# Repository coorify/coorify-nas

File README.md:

# coorify-nas

丐版 NAS,本项提供多种不同主板的 AIO 主机外壳模型及状态显示屏幕配套的软硬件资料，希望本项目能给以您一定的帮助！！！

## 支持主板

- 19026P

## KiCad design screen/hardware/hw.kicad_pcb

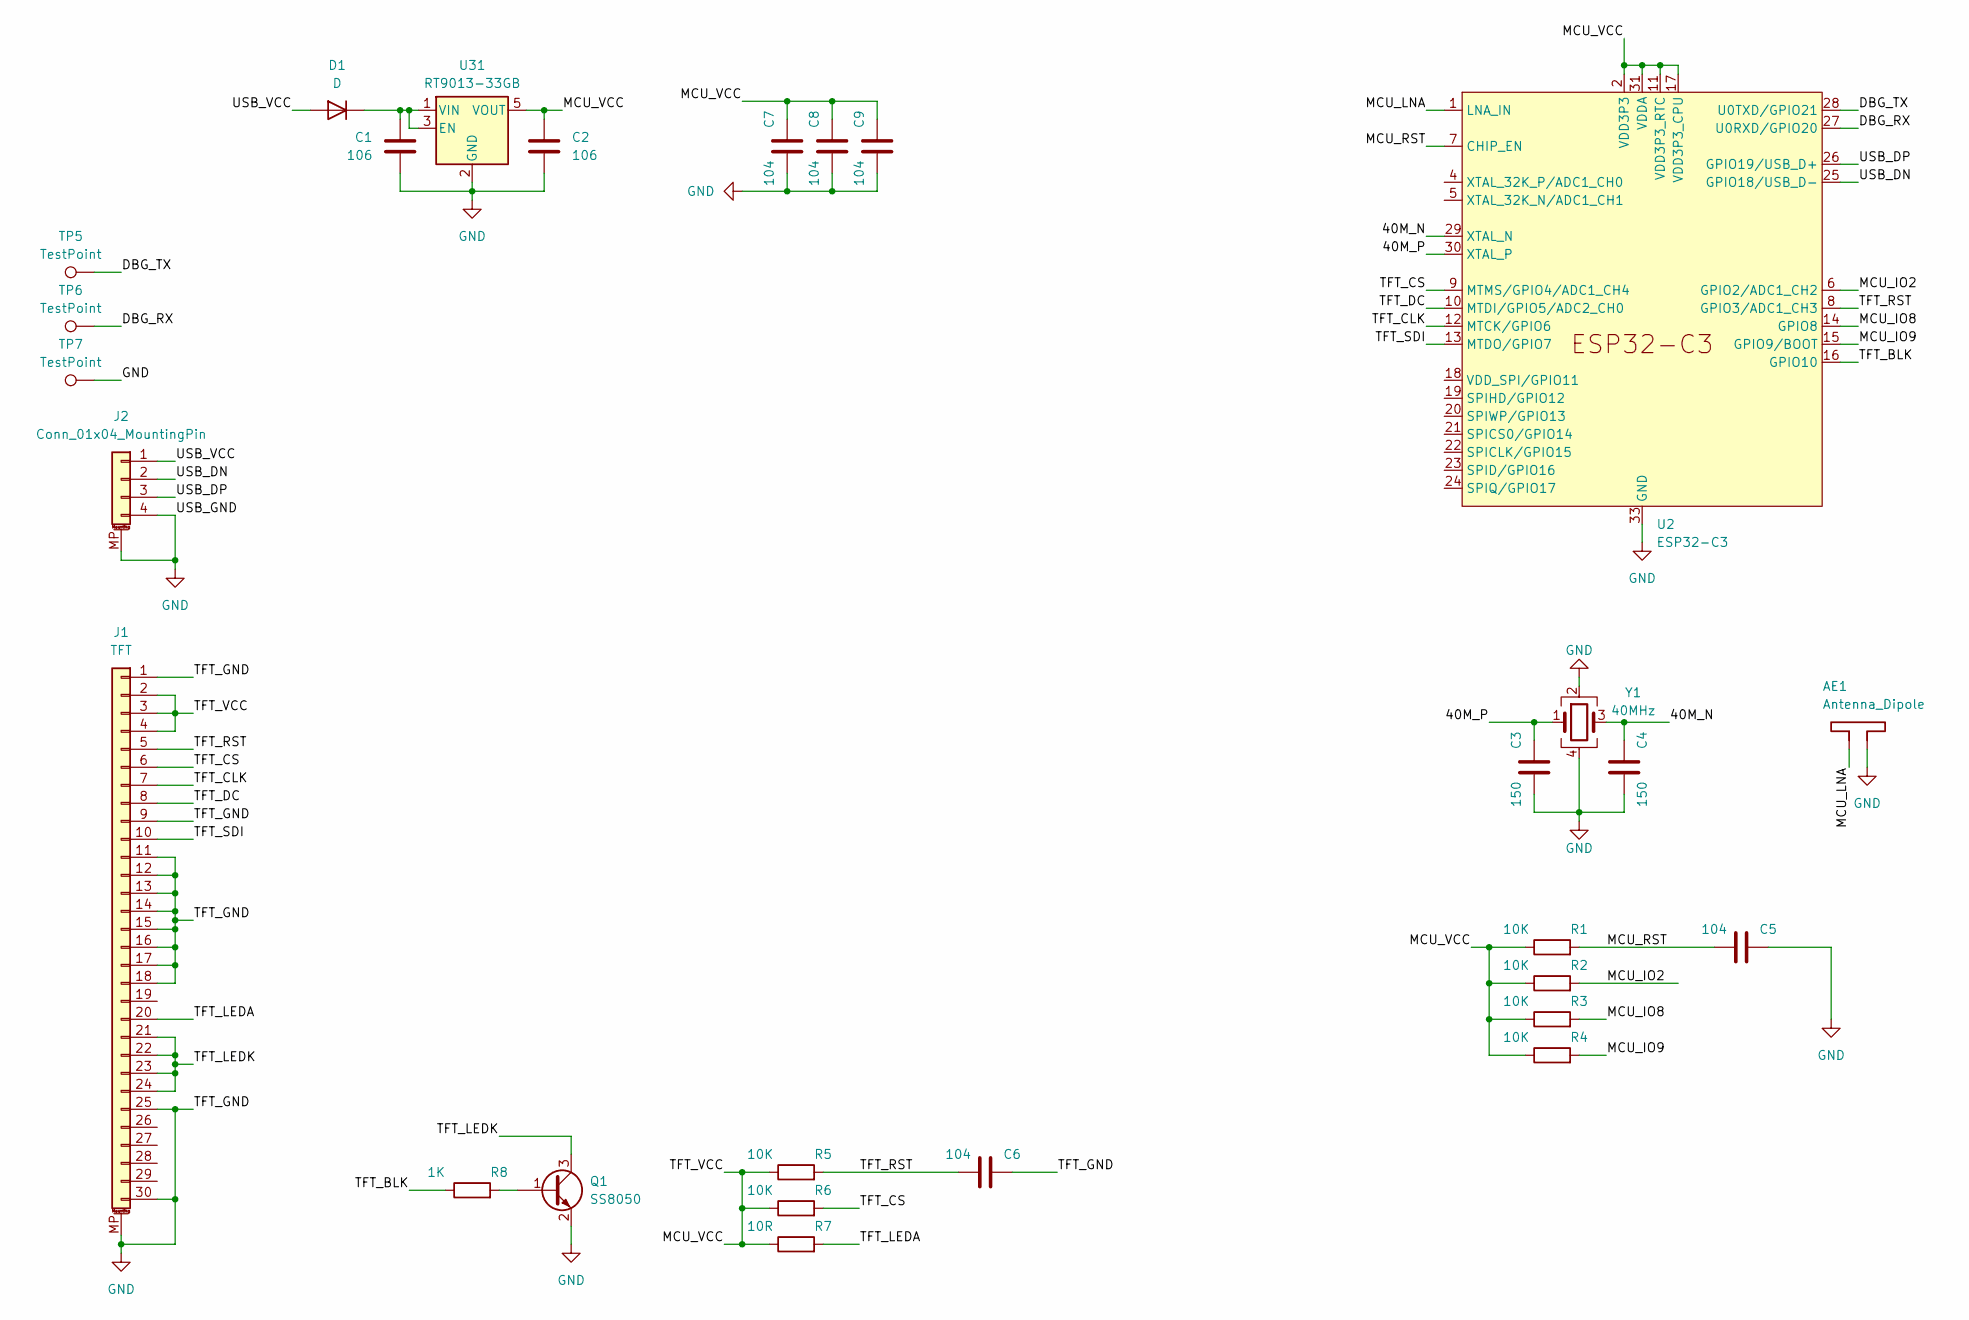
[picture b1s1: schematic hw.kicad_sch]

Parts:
AE1: Antenna_Dipole; Texas_SWRA117D_2.4GHz_Left
C1, C2: 106; C_0603_1608Metric
C3, C4: 150; C_0402_1005Metric
C5, C6, C7, C8, C9: 104; C_0402_1005Metric
D1: D; D_SOD-123
J1: TFT; Hirose_FH12-30S-0.5SH_1x30-1MP_P0.50mm_Horizontal
J2: Conn_01x04_MountingPin; JST_PH_B4B-PH-SM4-TB_1x04-1MP_P2.00mm_Vertical
Q1: SS8050; SOT-23
R1, R2, R3, R4, R5, R6: 10K; R_0402_1005Metric
R7: 10R; R_0402_1005Metric
R8: 1K; R_0402_1005Metric
TP5, TP6, TP7: TestPoint; TestPoint_Pad_D1.0mm
U2: ESP32-C3; QFN-32-1EP_5x5mm_P0.5mm_EP3.45x3.45mm
U31: RT9013-33GB; SOT-23-5
Y1: 40MHz; Crystal_SMD_2016-4Pin_2.0x1.6mm

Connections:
/40M_N: C4.2, U2.29 (XTAL_N), Y1.3
/40M_P: C3.2, U2.30 (XTAL_P), Y1.1
/DBG_RX: TP6.1, U2.27 (U0RXD/GPIO20)
/DBG_TX: TP5.1, U2.28 (U0TXD/GPIO21)
/MCU_IO2: R2.2, U2.6 (GPIO2/ADC1_CH2)
/MCU_IO8: R3.2, U2.14 (GPIO8)
/MCU_IO9: R4.2, U2.15 (GPIO9/BOOT)
/MCU_LNA: AE1.1, U2.1 (LNA_IN)
/MCU_RST: C5.1, R1.2, U2.7 (CHIP_EN)
/MCU_VCC: C2.1, C7.2, C8.2, C9.2, J1.2, J1.3, J1.4, R1.1, R2.1, R3.1, R4.1, R5.1, R6.1, R7.1, U2.2 (VDD3P3), U2.3 (VDD3P3), U2.11 (VDD3P3_RTC), U2.17 (VDD3P3_CPU), U2.31 (VDDA), U2.32 (VDDA); also elsewhere on the board
/TFT_BLK: R8.1, U2.16 (GPIO10)
/TFT_CLK: J1.7, U2.12 (MTCK/GPIO6)
/TFT_CS: J1.6, R6.2, U2.9 (MTMS/GPIO4/ADC1_CH4)
/TFT_DC: J1.8, U2.10 (MTDI/GPIO5/ADC2_CH0)
/TFT_LEDA: J1.20, R7.2
/TFT_LEDK: J1.21, J1.22, J1.23, J1.24, Q1.3 (C)
/TFT_RST: C6.1, J1.5, R5.2, U2.8 (GPIO3/ADC1_CH3)
/TFT_SDI: J1.10, U2.13 (MTDO/GPIO7)
/USB_DN: J2.2, U2.25 (GPIO18/USB_D-)
/USB_DP: J2.3, U2.26 (GPIO19/USB_D+)
/USB_VCC: D1.2 (A), J2.1
GND: AE1.2, C1.2, C2.2, C3.1, C4.1, C5.2, C6.2, C7.1, C8.1, C9.1, J1.1, J1.9, J1.11, J1.12, J1.13, J1.14, J1.15, J1.16, J1.17, J1.18, J1.25, J1.30, J1.MP (MountPin), J2.4, J2.MP (MountPin), Q1.2 (E), TP7.1, U2.33 (GND), Y1.2, Y1.4; also elsewhere on the board
unnamed 22: C1.1, D1.1 (K); also elsewhere on the board
unnamed: Q1.1 (B), R8.2

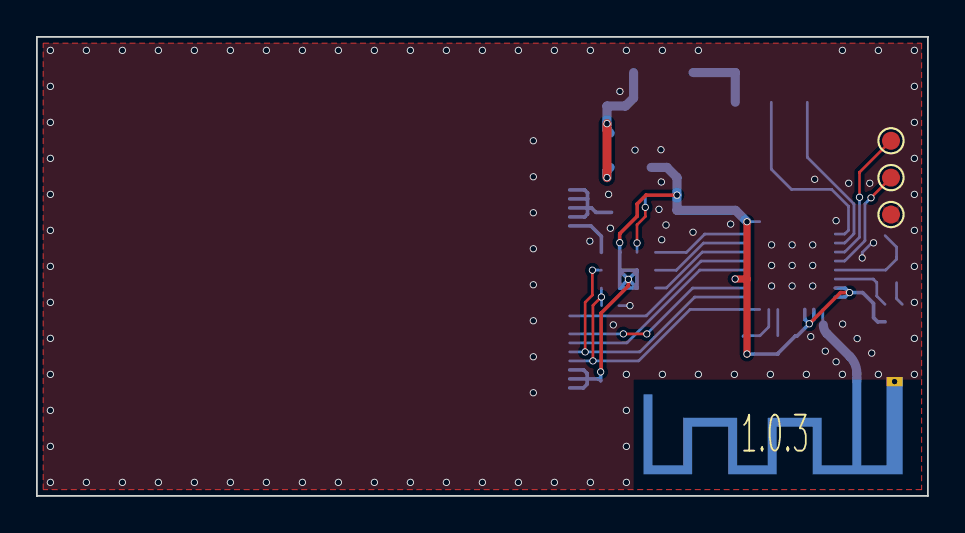
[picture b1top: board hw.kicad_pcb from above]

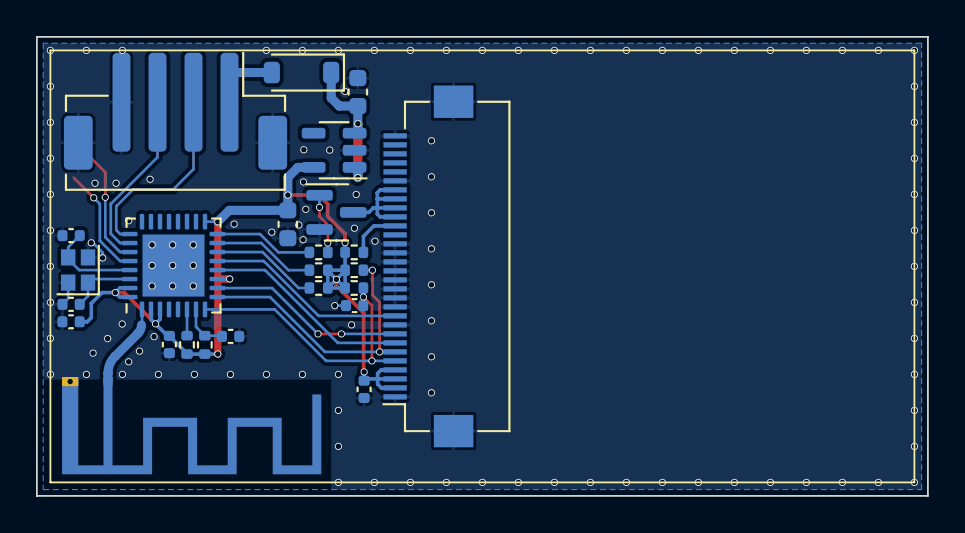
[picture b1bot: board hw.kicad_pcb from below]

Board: 2 copper layers, 49.5 x 25.5 mm, 28 parts (25 on the bottom side), 24 nets.

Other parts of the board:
U1: RT9013-33GB; SOT-23-5

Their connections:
/MCU_VCC: U1.5 (VOUT); also elsewhere on the board
GND: U1.2 (GND); also elsewhere on the board
unnamed 22: U1.1 (VIN), U1.3 (EN); also elsewhere on the board

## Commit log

2024-03-14 fisrt commit
2024-03-15 add hardware
2024-03-15 update docs
2024-03-15 add docs
